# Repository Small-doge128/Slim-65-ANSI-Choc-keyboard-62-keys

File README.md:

# about

A mint sounding keyboard that's small, lightweight and thin as a cookie, also the hardest was that I used ki cad , building a keyboard and software all of that first in my life. It's going to be for my acer aspire 5. 

# features

Hot swap sockets so you can swap switches fast and easy. You can program the keys to what ever you want via QMK, if you know what are you doing. Custom 3d prnted keycaps that i designed myself except the 1u I bought those and a 3d printed case that you can use but i didn't.

# step by step tutorial for firmware

1. Download the file called slim65_default.uf2.
2. Press and hold the boot button, while holding plug a USB-C cable from your computer to the controller.
3. Now a new folder/device should pop up.
4. Put the .uf2 file into there and it should remove it self.
5. If it did now the keyboard should work enjoy.

# dimensions
PCB - 294 mm lenght and 91 mm width

# keys

it has 49-1U keys, 6-1.25U keys, 2-1.5U keys, 2-1.75U keys, 2-2.25 and  1-6.25U key total 62 keys.

# why did i create it

I created this becouse i wanted a keyboard that i would like and enjoy. It's going to be a massive upgrade from my scissor keyboard on my laptop. I chose slim and 65% keyboard becouse i want it to be compact and light weight. I also like doing projects but this one is something else.

# pictures

# demo video

https://github.com/user-attachments/assets/ab127268-83f5-4e21-8910-376c34ff119f
This was my first demo video, so excuse my english and my stuttering.

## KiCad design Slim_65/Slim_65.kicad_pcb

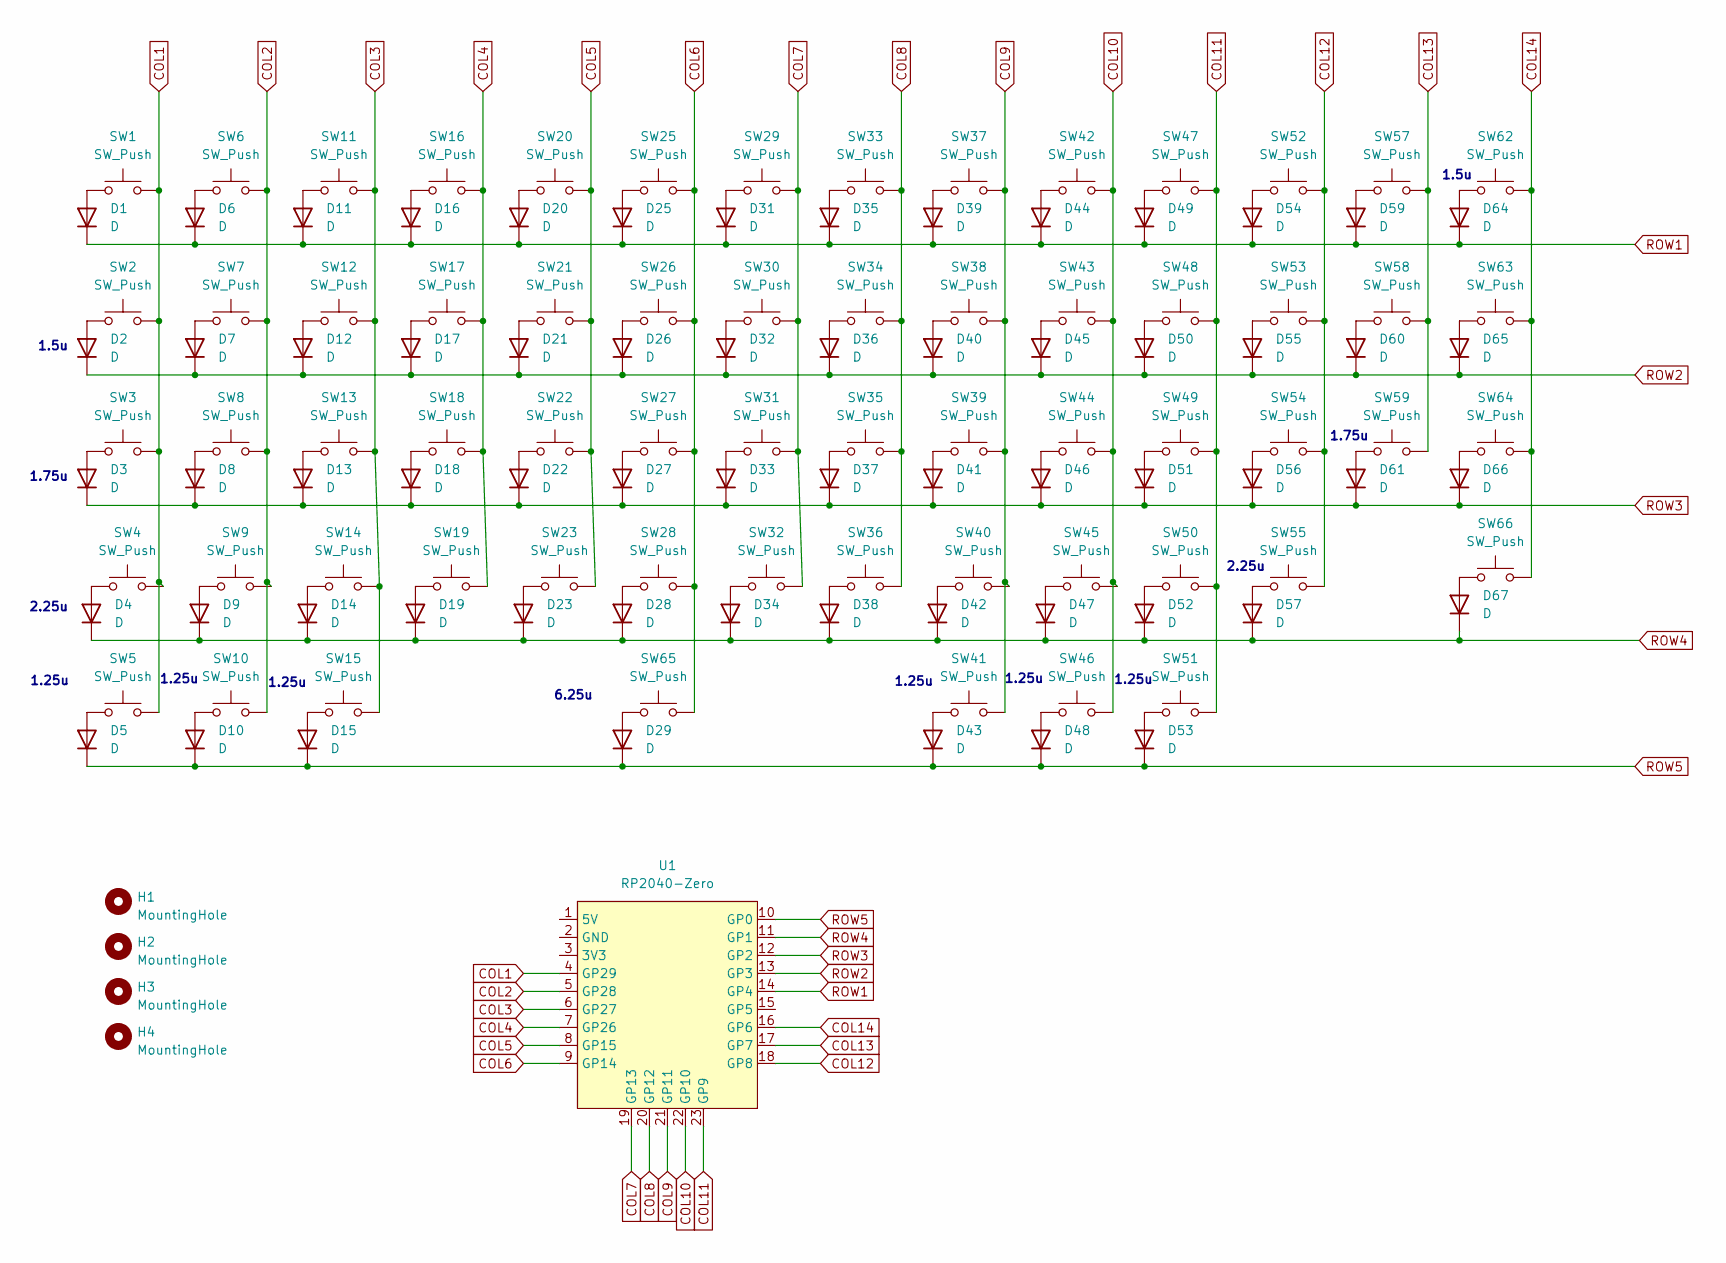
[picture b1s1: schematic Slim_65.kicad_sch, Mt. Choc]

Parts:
D1, D2, D3, D4, D5, D6, D7, D8, D9, D10, D11, D12, D13, D14, D15, D16, D17, D18, D19, D20, D21, D22, D23, D25, D26, D27, D28, D29, D31, D32, D33, D34, D35, D36, D37, D38, D39, D40, D41, D42, D43, D44, D45, D46, D47, D48, D49, D50, D51, D52, D53, D54, D55, D56, D57, D59, D60, D61, D64, D65, D66, D67: D; D_SOD123
H1, H2, H3, H4: MountingHole; m2_standoff
SW1, SW6, SW7, SW8, SW9, SW11, SW12, SW13, SW14, SW16, SW17, SW18, SW19, SW20, SW21, SW22, SW23, SW25, SW26, SW27, SW28, SW29, SW30, SW31, SW32, SW33, SW34, SW35, SW36, SW37, SW38, SW39, SW40, SW42, SW43, SW44, SW45, SW47, SW48, SW49, SW50, SW52, SW53, SW54, SW57, SW58, SW63, SW64, SW66: SW_Push; Choc-1u
SW2, SW62: SW_Push; Choc-1.5u
SW3, SW59: SW_Push; Choc-1.75u
SW4, SW55: SW_Push; Choc-2.25u
SW5, SW10, SW15, SW41, SW46, SW51: SW_Push; Choc-1.25u
SW65: SW_Push; Choc-6.25u
U1: RP2040-Zero; RP2040 Zero

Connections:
COL1: SW1.2, SW2.2, SW3.2, SW4.2, SW5.2, U1.4 (GP29)
COL2: SW6.2, SW7.2, SW8.2, SW9.2, SW10.2, U1.5 (GP28)
COL3: SW11.2, SW12.2, SW13.2, SW14.2, SW15.2, U1.6 (GP27)
COL4: SW16.2, SW17.2, SW18.2, SW19.2, U1.7 (GP26)
COL5: SW20.2, SW21.2, SW22.2, SW23.2, U1.8 (GP15)
COL6: SW25.2, SW26.2, SW27.2, SW28.2, SW65.2, U1.9 (GP14)
COL7: SW29.2, SW30.2, SW31.2, SW32.2, U1.19 (GP13)
COL8: SW33.2, SW34.2, SW35.2, SW36.2, U1.20 (GP12)
COL9: SW37.2, SW38.2, SW39.2, SW40.2, SW41.2, U1.21 (GP11)
COL10: SW42.2, SW43.2, SW44.2, SW45.2, SW46.2, U1.22 (GP10)
COL11: SW47.2, SW48.2, SW49.2, SW50.2, SW51.2, U1.23 (GP9)
COL12: SW52.2, SW53.2, SW54.2, SW55.2, U1.18 (GP8)
COL13: SW57.2, SW58.2, SW59.2, U1.17 (GP7)
COL14: SW62.2, SW63.2, SW64.2, SW66.2, U1.16 (GP6)
unnamed: D1.2 (A), SW1.1
unnamed: D2.2 (A), SW2.1
unnamed: D3.2 (A), SW3.1
unnamed: D4.2 (A), SW4.1
unnamed: D5.2 (A), SW5.1
unnamed: D6.2 (A), SW6.1
unnamed: D7.2 (A), SW7.1
unnamed: D8.2 (A), SW8.1
unnamed: D9.2 (A), SW9.1
unnamed: D10.2 (A), SW10.1
unnamed: D11.2 (A), SW11.1
unnamed: D12.2 (A), SW12.1
unnamed: D13.2 (A), SW13.1
unnamed: D14.2 (A), SW14.1
unnamed: D15.2 (A), SW15.1
unnamed: D16.2 (A), SW16.1
unnamed: D17.2 (A), SW17.1
unnamed: D18.2 (A), SW18.1
unnamed: D19.2 (A), SW19.1
unnamed: D20.2 (A), SW20.1
unnamed: D21.2 (A), SW21.1
unnamed: D22.2 (A), SW22.1
unnamed: D23.2 (A), SW23.1
unnamed: D25.2 (A), SW25.1
unnamed: D26.2 (A), SW26.1
unnamed: D27.2 (A), SW27.1
unnamed: D28.2 (A), SW28.1
unnamed: D29.2 (A), SW65.1
unnamed: D31.2 (A), SW29.1
unnamed: D32.2 (A), SW30.1
unnamed: D33.2 (A), SW31.1
unnamed: D34.2 (A), SW32.1
unnamed: D35.2 (A), SW33.1
unnamed: D36.2 (A), SW34.1
unnamed: D37.2 (A), SW35.1
unnamed: D38.2 (A), SW36.1
unnamed: D39.2 (A), SW37.1
unnamed: D40.2 (A), SW38.1
unnamed: D41.2 (A), SW39.1
unnamed: D42.2 (A), SW40.1
unnamed: D43.2 (A), SW41.1
unnamed: D44.2 (A), SW42.1
unnamed: D45.2 (A), SW43.1
unnamed: D46.2 (A), SW44.1
unnamed: D47.2 (A), SW45.1
unnamed: D48.2 (A), SW46.1
unnamed: D49.2 (A), SW47.1
unnamed: D50.2 (A), SW48.1
unnamed: D51.2 (A), SW49.1
unnamed: D52.2 (A), SW50.1
unnamed: D53.2 (A), SW51.1
unnamed: D54.2 (A), SW52.1
unnamed: D55.2 (A), SW53.1
unnamed: D56.2 (A), SW54.1
unnamed: D57.2 (A), SW55.1
unnamed: D59.2 (A), SW57.1
unnamed: D60.2 (A), SW58.1
unnamed: D61.2 (A), SW59.1
unnamed: D64.2 (A), SW62.1
unnamed: D65.2 (A), SW63.1
unnamed: D66.2 (A), SW64.1
unnamed: D67.2 (A), SW66.1
ROW1: D1.1 (K), D6.1 (K), D11.1 (K), D16.1 (K), D20.1 (K), D25.1 (K), D31.1 (K), D35.1 (K), D39.1 (K), D44.1 (K), D49.1 (K), D54.1 (K), D59.1 (K), D64.1 (K), U1.14 (GP4)
ROW2: D2.1 (K), D7.1 (K), D12.1 (K), D17.1 (K), D21.1 (K), D26.1 (K), D32.1 (K), D36.1 (K), D40.1 (K), D45.1 (K), D50.1 (K), D55.1 (K), D60.1 (K), D65.1 (K), U1.13 (GP3)
ROW3: D3.1 (K), D8.1 (K), D13.1 (K), D18.1 (K), D22.1 (K), D27.1 (K), D33.1 (K), D37.1 (K), D41.1 (K), D46.1 (K), D51.1 (K), D56.1 (K), D61.1 (K), D66.1 (K), U1.12 (GP2)
ROW4: D4.1 (K), D9.1 (K), D14.1 (K), D19.1 (K), D23.1 (K), D28.1 (K), D34.1 (K), D38.1 (K), D42.1 (K), D47.1 (K), D52.1 (K), D57.1 (K), D67.1 (K), U1.11 (GP1)
ROW5: D5.1 (K), D10.1 (K), D15.1 (K), D29.1 (K), D43.1 (K), D48.1 (K), D53.1 (K), U1.10 (GP0)

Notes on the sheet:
1.5u
1.25u
6.25u
2.25u
1.75u

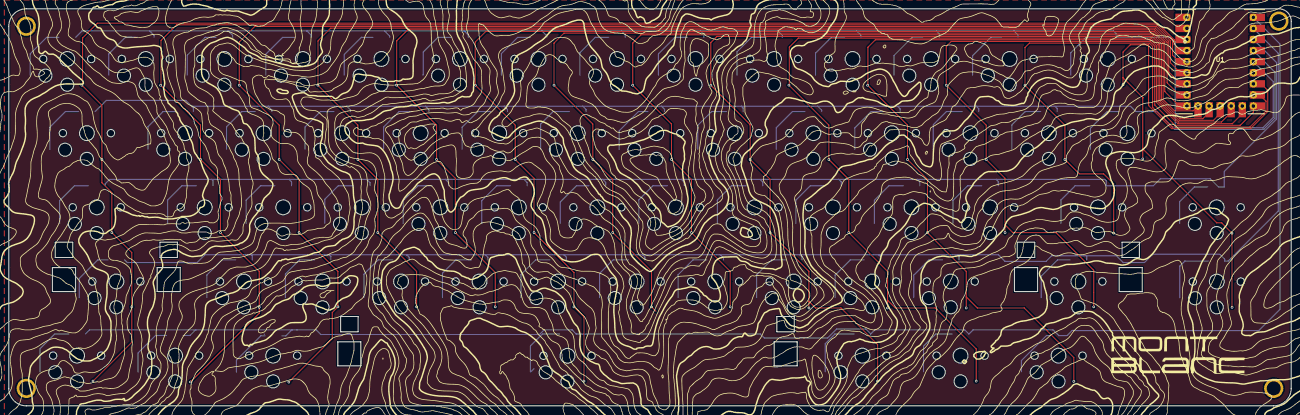
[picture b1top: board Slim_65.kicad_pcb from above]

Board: 2 copper layers, 293.9 x 91.0 mm, 130 parts (0 on the bottom side), 81 nets.

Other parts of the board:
g```: LOGO; mont

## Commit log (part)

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2026-05-09 Create mont blanc keyboard

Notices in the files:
Slim_65/Slim_65.kicad_pcb:
License: MIT
